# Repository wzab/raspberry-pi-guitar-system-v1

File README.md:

raspberry-pi-guitar-system-v1
=============================

Open Hardware/Open Software extension board for Raspberry Pi to connect an electric guitar to a virtual amplifier via network (e.g. WiFi)

The idea of this system was presented in the thread: https://groups.google.com/forum/#!topic/comp.sys.raspberry-pi/EgQAQ0DNwN4

The repository will contain both Kicad project of the hardware, and sources of the software.

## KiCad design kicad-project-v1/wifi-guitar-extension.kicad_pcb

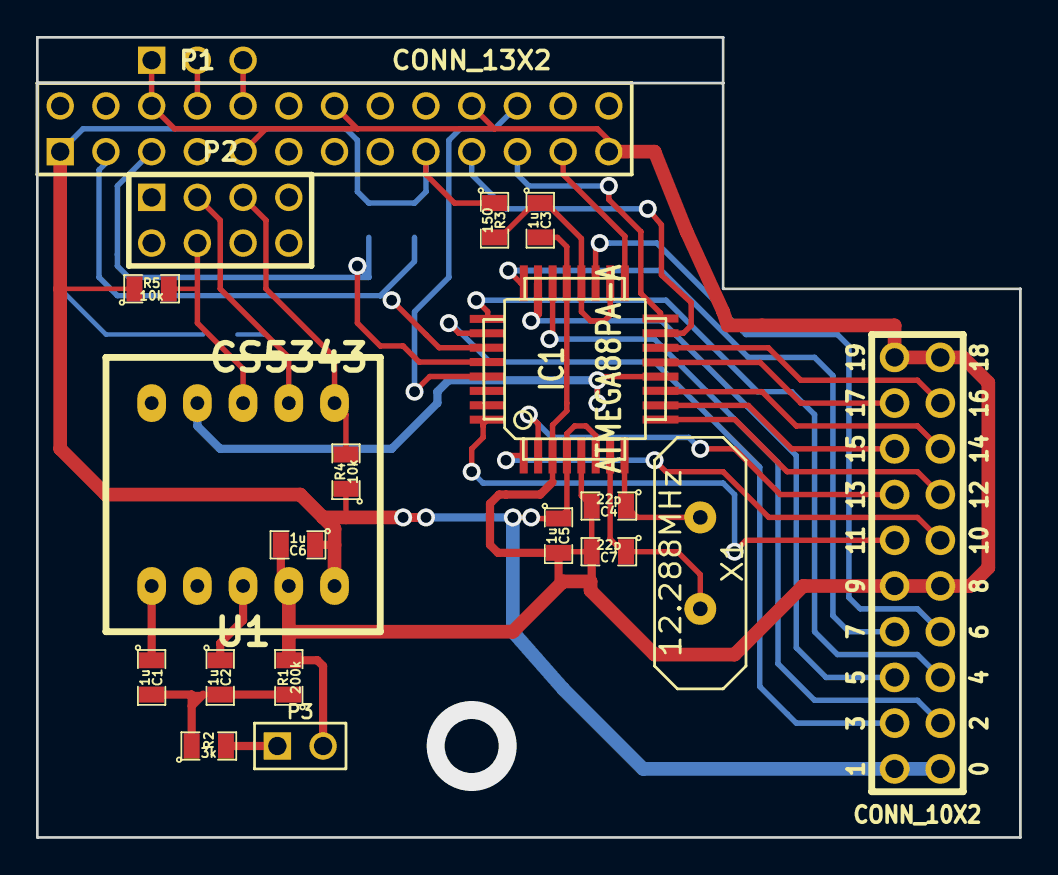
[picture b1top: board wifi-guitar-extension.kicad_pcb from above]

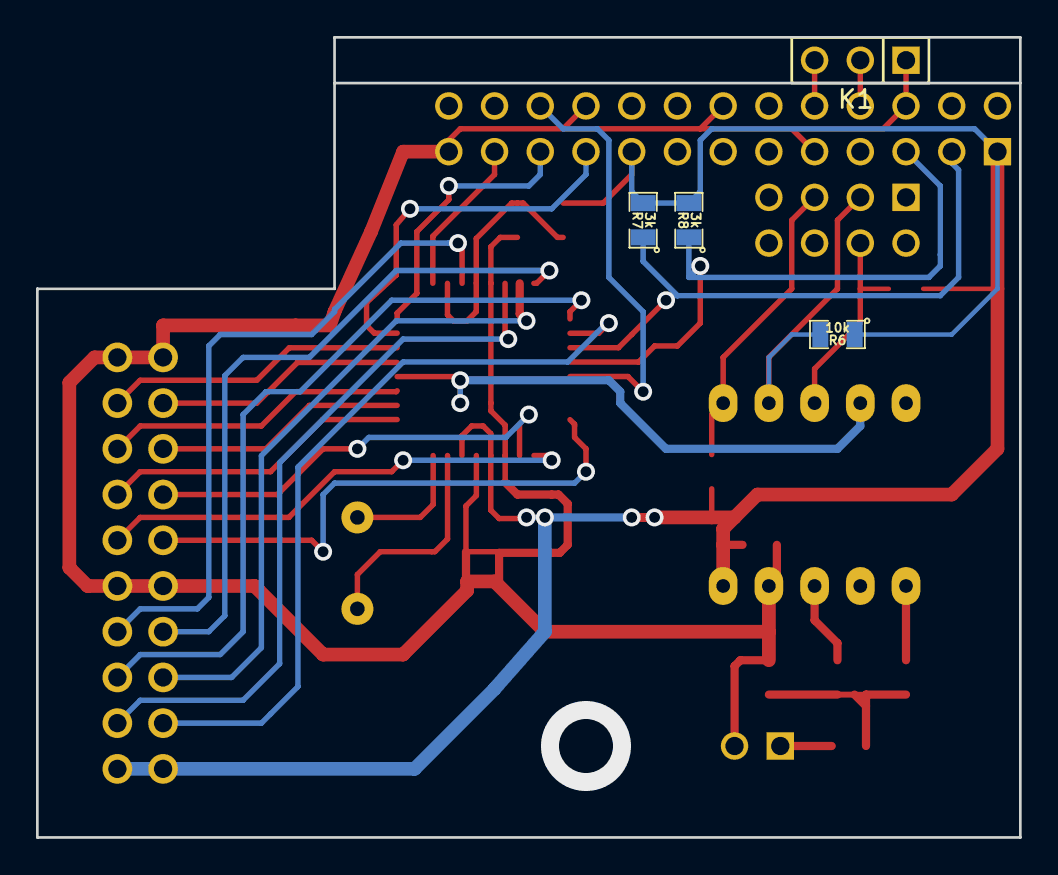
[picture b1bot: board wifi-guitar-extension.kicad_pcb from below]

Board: 2 copper layers, 54.6 x 44.4 mm, 23 parts (4 on the bottom side), 35 nets.

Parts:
C1, C2, C3, C5, C6: 1u; SM0805
C4, C7: 22p; SM0805
IC1: ATMEGA88PA-A; TQFP32
K1: CONN_3; PIN_ARRAY_3X1
P1: CONN_13X2; pin_array_13x2
P2: CONN_4X2; pin_array_4x2_reversed
P3: CONN_2; PIN_ARRAY_2X1
P4: CONN_10X2; Pin_Array_Port_10x2_Opendous
R1: 200k; SM0805
R2, R7, R8: 3k; SM0805
R3: 150; SM0805
R4, R5, R6: 10k; SM0805
U1: CS5343; CS5343_4-DTBRD
X1: 12.288MHz; HC-18UV

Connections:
/CS5343_MCLK: IC1.12, U1.4
/POT_1: IC1.22, P4.3
/POT_2: IC1.26, P4.4
/POT_3: IC1.25, P4.5
/POT_4: IC1.23, P4.6
/POT_5: IC1.19, P4.7
/POT_6: IC1.24, P4.8
/RPI_PCM_CLK: P2.3, R6.2, U1.2
/RPI_PCM_DIN: P2.5, R4.2, U1.1
/RPI_PCM_FS: P2.4, R5.2, U1.3
/RPI_RXD: K1.3, P1.10
/RPI_SCL: IC1.28, P1.5, R8.1
/RPI_SDA: IC1.27, P1.3, R7.1
/RPI_TXD: K1.2, P1.8
/RPI_uC_MISO: IC1.16, P1.21
/RPI_uC_MOSI: IC1.15, P1.19
/RPI_uC_RESET: IC1.29, P1.22
/RPI_uC_SCK: IC1.17, P1.23
/SW1: IC1.1, P4.11
/SW2: IC1.32, P4.12
/SW3: IC1.9, P4.13
/SW4: IC1.2, P4.14
/SW5: IC1.11, P4.15
/SW6: IC1.10, P4.16
/SW7: IC1.14, P4.17
/SW8: IC1.13, P4.18
/V3,3: C5.1, C6.1, IC1.4, IC1.6, P1.1, P1.17, P4.1, P4.2, R3.1, R4.1, R5.1, R6.1, R7.2, R8.2, U1.10
GND: C3.2, C4.2, C5.2, C6.2, C7.2, IC1.3, IC1.5, IC1.21, K1.1, P1.6, P1.9, P1.14, P1.20, P1.25, P3.2, P4.9, P4.10, P4.19, P4.20, R1.2, U1.9
unnamed: C7.1, IC1.7, X1.2
unnamed: C1.1, U1.6
unnamed: C2.1, U1.8
unnamed: P3.1, R2.2
unnamed: C1.2, C2.2, R1.1, R2.1
unnamed: C3.1, IC1.18, IC1.20, R3.2
unnamed: C4.1, IC1.8, X1.1

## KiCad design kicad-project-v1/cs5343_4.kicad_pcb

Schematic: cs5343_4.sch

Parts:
C1, C5, C7: 100n
C2, C6, C8: 1u
C3, C4: 180p
P1, P2: CONN_5
U1: CS5343; TSSOP-10

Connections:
GND: C1.2, C2.2, C3.2, C4.2, C5.2, C6.2, C7.2, C8.2, P2.2, U1.9 (GND)
unnamed: C3.1, P2.3, U1.8 (AINR)
unnamed: P1.4, U1.4 (MCLK)
unnamed: P1.3, U1.3 (LRCK)
unnamed: P1.2, U1.2 (SCLK)
unnamed: P1.1, U1.1 (SDOUT)
unnamed: C7.1, C8.1, P2.1, U1.10 (VA)
unnamed: C5.1, C6.1, P2.4, U1.7 (VQ)
unnamed: C1.1, C2.1, P1.5, U1.5 (FILT+)
unnamed: C4.1, P2.5, U1.6 (AINL)

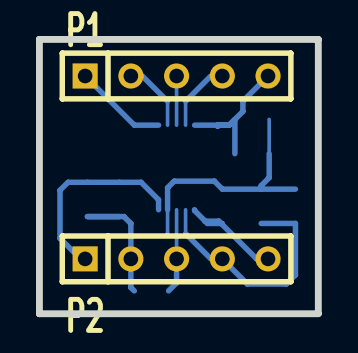
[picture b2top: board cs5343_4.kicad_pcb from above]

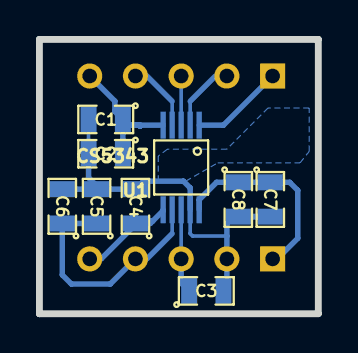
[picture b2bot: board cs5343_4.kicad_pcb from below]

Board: 2 copper layers, 15.5 x 15.2 mm, 11 parts (9 on the bottom side), 10 nets.

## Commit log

2013-11-03 Commited first version of schematic and PCB design. Please note, that this version uses ATmega88 uC, running at 3.3V Vcc and 12.288 MHz clock. The ATmega88 uC is used as: 1. Clock source for CS5343/4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
    State of switches and potentiometers is reported do RPi via
    I2C interface (ATmega is I2C slave).
    ATmega may be programmed from the RPi using the avrdude program,
    as described in
    http://kevincuzner.com/2013/05/27/raspberry-pi-as-an-avr-programmer/
2013-12-26 Added resistor pulling up the SDOUT line in CS534x (to ensure the Master Mode). Added optional connector for connecting the UART.
2013-12-27 Added directory for ATmega88p firmware
